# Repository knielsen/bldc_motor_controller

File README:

Simple board to control a BLDC (brushless motor).

Based on Texas Instruments TM4C1232 MCU and ST L6234 motor controller.

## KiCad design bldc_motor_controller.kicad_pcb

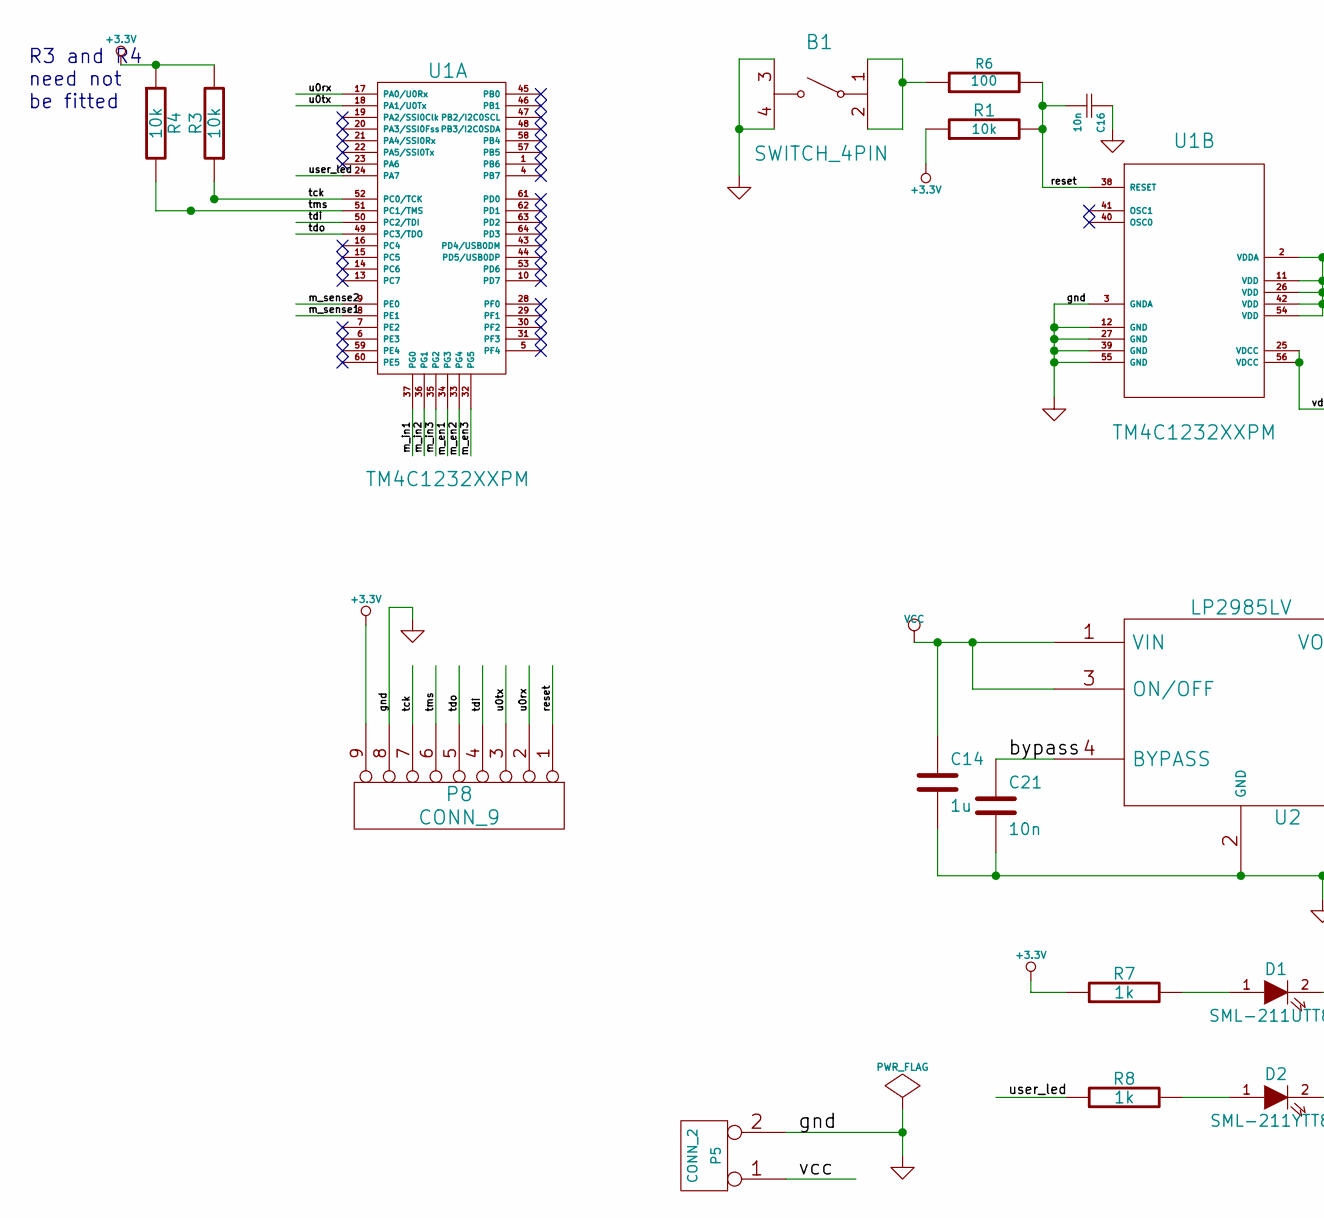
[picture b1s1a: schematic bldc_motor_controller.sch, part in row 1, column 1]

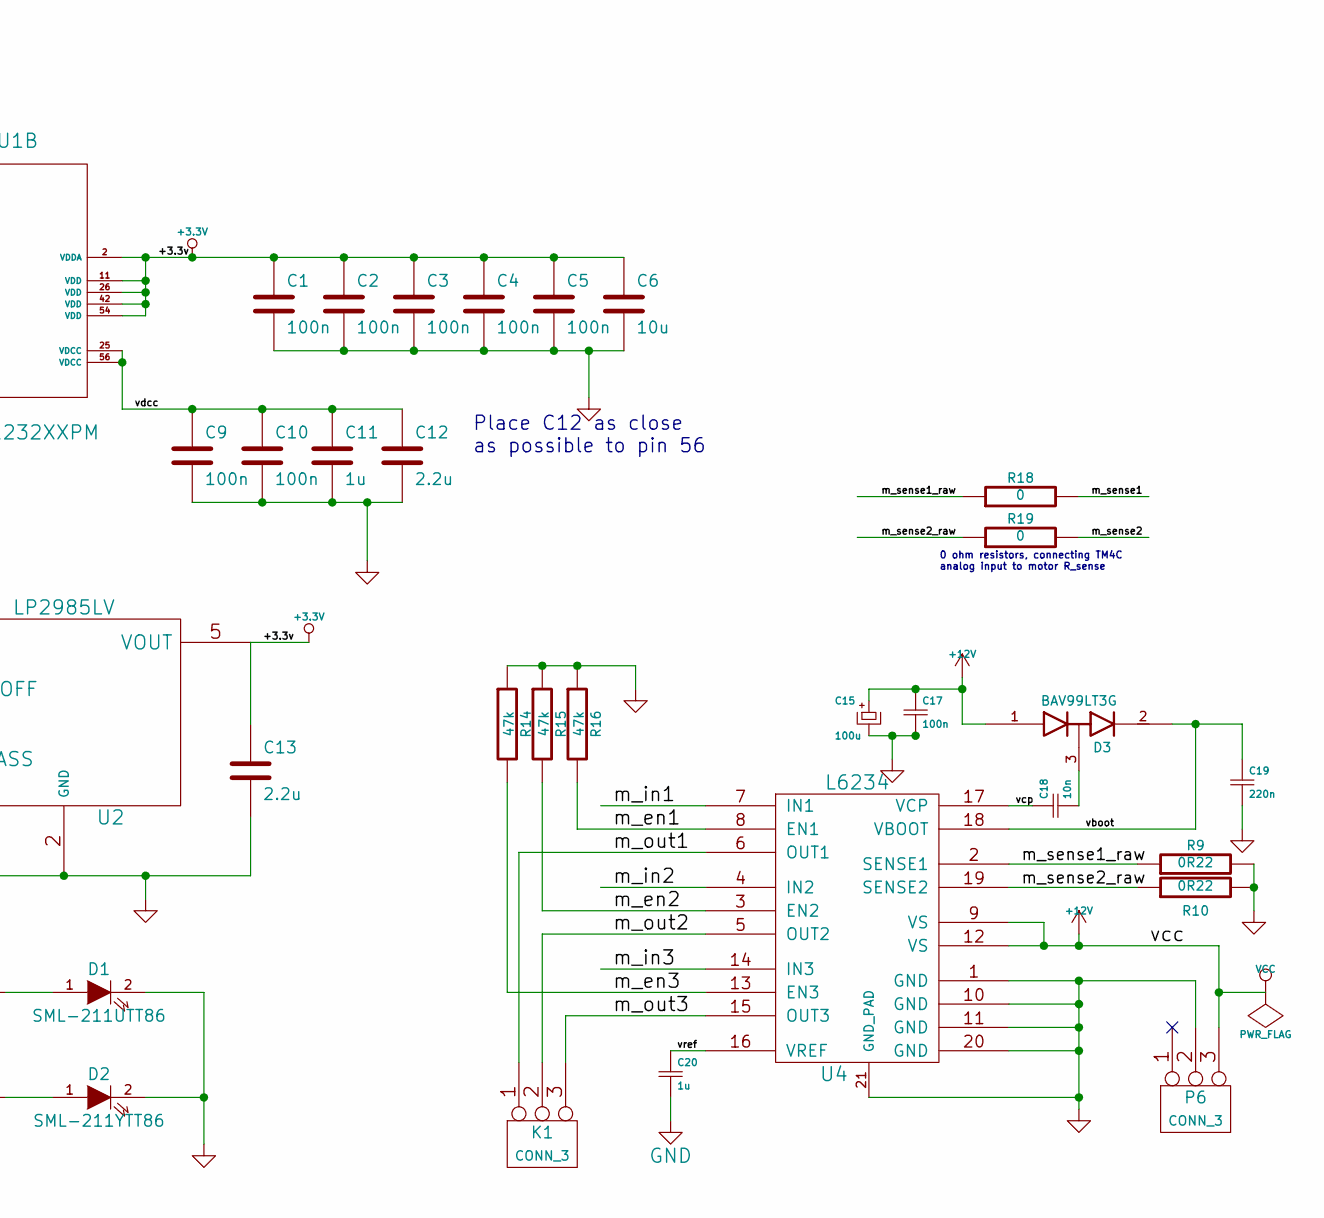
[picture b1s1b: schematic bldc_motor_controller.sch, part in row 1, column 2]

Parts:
B1: SWITCH_4PIN; SWITCH_FSMJSMA
C1, C2, C3, C4, C5, C9, C10, C17: 100n; c_0805
C6: 10u; c_0805
C11, C14, C20: 1u; c_0805
C12, C13: 2.2u; c_0805
C15: 100u; c_elec_6.3x5.3
C16, C18, C21: 10n; c_0805
C19: 220n; c_0805
D1: SML-211UTT86; Led_0805
D2: SML-211YTT86; Led_0805
D3: BAV99LT3G; SOT-23
K1: CONN_3; pin_strip_3
P5: CONN_2; pin_strip_2
P6: CONN_3; dc_socket
P8: CONN_9; pin_strip_9
R1, R3, R4: 10k; r_0805
R6: 100; r_0805
R7, R8: 1k; r_0805
R9, R10: 0R22; r_0805
R14, R15, R16: 47k; r_0805
R18, R19: 0; r_0805
U1: TM4C1232XXPM; TQFP-64
U2: LP2985LV; SOT-23-5
U4: L6234; POWERSO20

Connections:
+3.3V: C1.1, C2.1, C3.1, C4.1, C5.1, C6.1, C13.1, P8.9, R1.1, R3.2, R4.1, R7.1, U1.2 (VDDA), U1.11 (VDD), U1.26 (VDD), U1.42 (VDD), U1.54 (VDD), U2.5 (VOUT)
/bypass: C21.1, U2.4 (BYPASS)
/m_en1: R16.2, U1.34 (PG3), U4.8 (EN1)
/m_en2: R15.2, U1.33 (PG4), U4.3 (EN2)
/m_en3: R14.2, U1.32 (PG5), U4.13 (EN3)
/m_in1: U1.37 (PG0), U4.7 (IN1)
/m_in2: U1.36 (PG1), U4.4 (IN2)
/m_in3: U1.35 (PG2), U4.14 (IN3)
/m_out1: K1.1, U4.6 (OUT1)
/m_out2: K1.2 (PM), U4.5 (OUT2)
/m_out3: K1.3, U4.15 (OUT3)
/m_sense1: R18.2, U1.8 (PE1)
/m_sense1_raw: R9.1, R18.1, U4.2 (SENSE1)
/m_sense2: R19.2, U1.9 (PE0)
/m_sense2_raw: R10.1, R19.1, U4.19 (SENSE2)
/reset: C16.2, P8.1, R1.2, R6.2, U1.38 (RESET)
/tck: P8.7, R3.1, U1.52 (PC0/TCK)
/tdi: P8.4, U1.50 (PC2/TDI)
/tdo: P8.5, U1.49 (PC3/TDO)
/tms: P8.6, R4.2, U1.51 (PC1/TMS)
/u0rx: P8.2, U1.17 (PA0/U0Rx)
/u0tx: P8.3, U1.18 (PA1/U0Tx)
/user_led: R8.1, U1.24 (PA7)
/vboot: C19.1, D3.2 (cathode), U4.18 (VBOOT)
/vcp: C18.1, U4.17 (VCP)
/vdcc: C9.1, C10.1, C11.1, C12.1, U1.25 (VDCC), U1.56 (VDCC)
/vref: C20.1, U4.16 (VREF)
GND: B1.3, B1.4, C1.2, C2.2, C3.2, C4.2, C5.2, C6.2, C9.2, C10.2, C11.2, C12.2, C13.2, C14.2, C15.2, C16.1, C17.2, C19.2, C20.2, C21.2, D1.2 (K), D2.2 (K), P5.2 (PM), P6.2 (PM), P8.8, R9.2, R10.2, R14.1, R15.1, R16.1, U1.3 (GNDA), U1.12 (GND), U1.27 (GND), U1.39 (GND), U1.55 (GND), U2.2 (GND), U4.1 (GND), U4.10 (GND), U4.11 (GND), U4.20 (GND), U4.21 (GND_PAD)
unnamed: B1.1, B1.2, R6.1
unnamed: C18.2, D3.3 (AK)
unnamed: D1.1 (A), R7.2
unnamed: D2.1 (A), R8.2
VCC: C14.1, C15.1, C17.1, D3.1 (Anode), P5.1, P6.3, U2.1 (VIN), U2.3 (ON/OFF), U4.9 (VS), U4.12 (VS)

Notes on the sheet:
Place C12 as close as possible to pin 56
0 ohm resistors, connecting TM4C analog input to motor R_sense
R3 and R4 need not be fitted

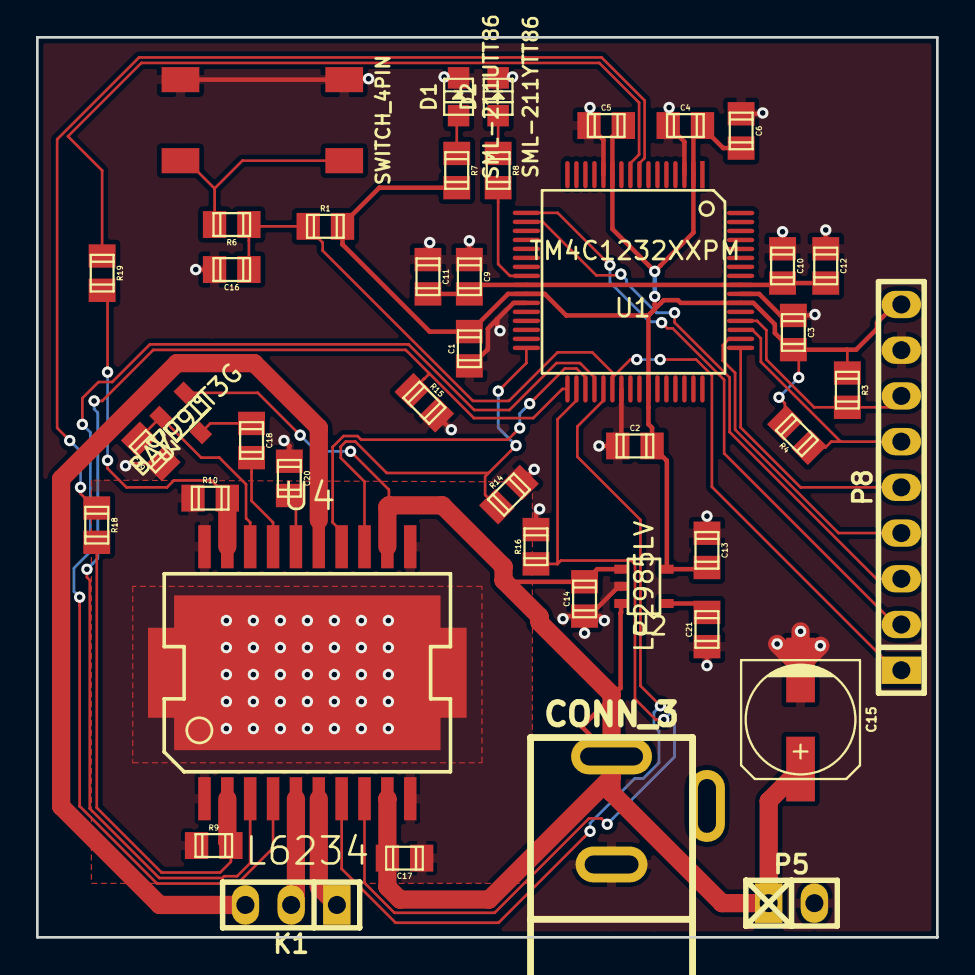
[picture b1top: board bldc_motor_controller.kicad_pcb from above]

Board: 2 copper layers, 50.0 x 50.0 mm, 43 parts (0 on the bottom side), 33 nets.

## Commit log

2015-02-08 First draft of PCB for BLDC motor.
2015-02-09 Fix proper wide tracks for m_sense, which carries all the motor currents.
